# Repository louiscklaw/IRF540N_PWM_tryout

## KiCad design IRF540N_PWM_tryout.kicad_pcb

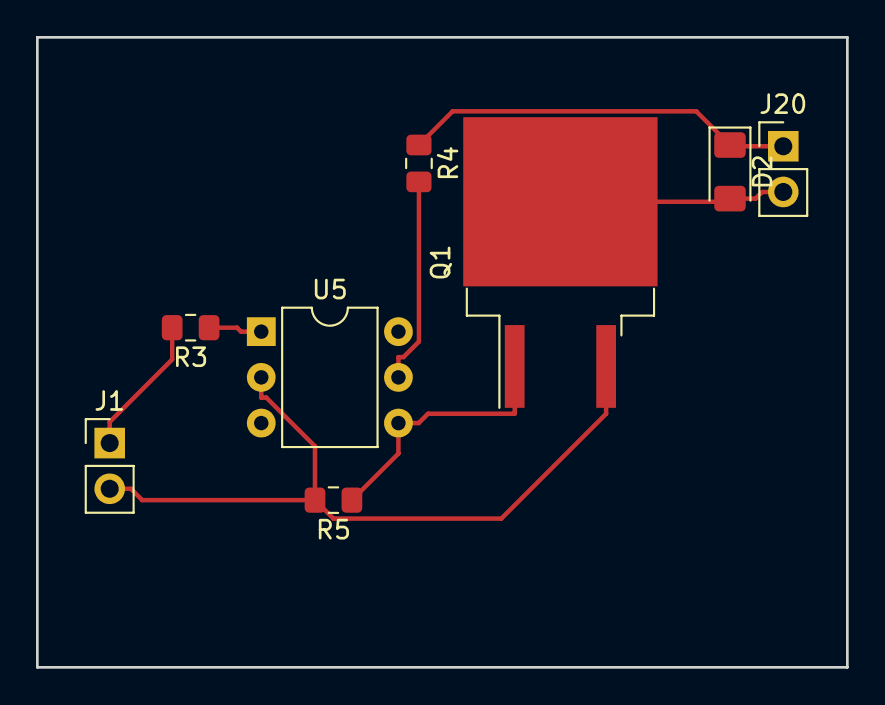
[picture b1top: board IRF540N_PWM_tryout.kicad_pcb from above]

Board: 2 copper layers, 45.0 x 35.0 mm, 8 parts (0 on the bottom side), 7 nets.

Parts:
D2: SD_SS510; D_1206_3216Metric_Pad1.42x1.75mm_HandSolder
J1: Conn_01x02; PinHeader_1x02_P2.54mm_Vertical
J20: PWM_TO_MOTOR; PinHeader_1x02_P2.54mm_Vertical
Q1: IRF540N; TO-263-2
R3: R330,0805; R_0805_2012Metric_Pad1.15x1.40mm_HandSolder
R4: R102,0805; R_0805_2012Metric_Pad1.15x1.40mm_HandSolder
R5: R103,0805; R_0805_2012Metric_Pad1.15x1.40mm_HandSolder
U5: 4N35; DIP-6_W7.62mm

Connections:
+12V: D2.1, J20.1, R4.1
GND: J1.2, Q1.3, R5.2, U5.2
unnamed: D2.2, J20.2, Q1.2
unnamed: Q1.1, R5.1, U5.4
unnamed: R3.1, U5.1
unnamed: R4.2, U5.5
Spindle: J1.1, R3.2

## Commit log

2018-12-04 update,
2020-05-05 ci: init travis build config,
2020-05-05 ci: init travis token,
